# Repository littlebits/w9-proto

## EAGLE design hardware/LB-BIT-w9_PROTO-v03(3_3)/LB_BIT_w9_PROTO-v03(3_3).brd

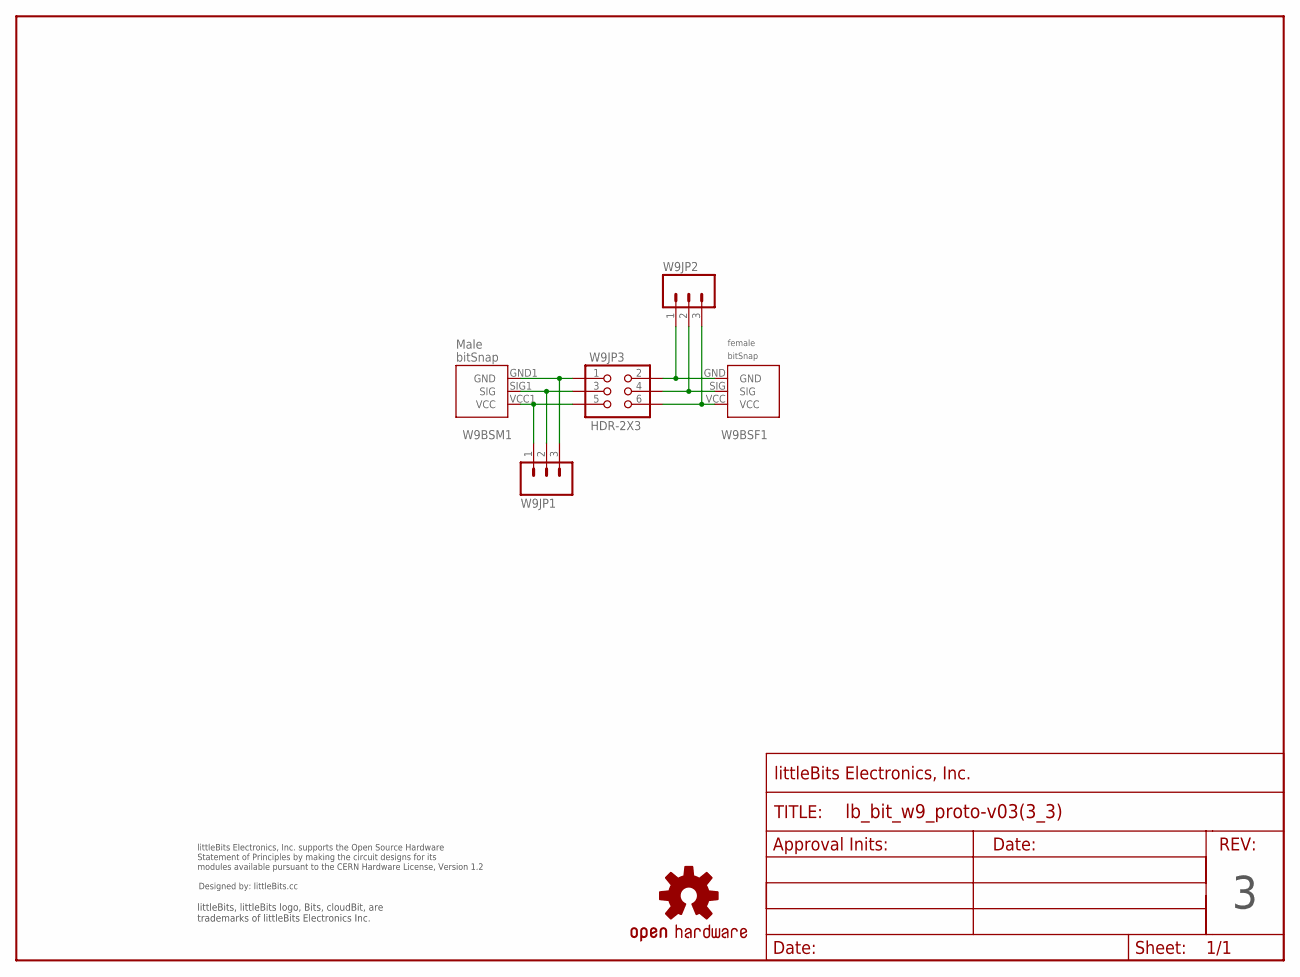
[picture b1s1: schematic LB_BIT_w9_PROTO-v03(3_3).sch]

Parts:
U$5: OSHWCREDIT
U$11: OSHW-LOGOL; OSHW-LOGO-L
U$13: FRAME-LETTER-OHWOHW; FABDWG01-OHW
W9BSF1: BITSNAP_V03_FEMALE"; BITSNAP_V03_FEMALE_NO_ARROW
W9BSM1: BITSNAP_V03_MALE
W9JP1, W9JP2: SCREW-TERMINAL-3PIN-2.54MM; 22-23-2031
W9JP3: HDR-2X3; 2X03

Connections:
GND1: W9BSM1.GND1 (GND), W9JP1.3, W9JP3.1
GND2: W9BSF1.GND, W9JP2.1, W9JP3.2
unnamed: W9BSM1.SIG1 (SIG), W9JP1.2, W9JP3.3
unnamed: W9BSM1.VCC1 (VCC), W9JP1.1, W9JP3.5
unnamed: W9BSF1.VCC, W9JP2.3, W9JP3.6
unnamed: W9BSF1.SIG, W9JP2.2, W9JP3.4

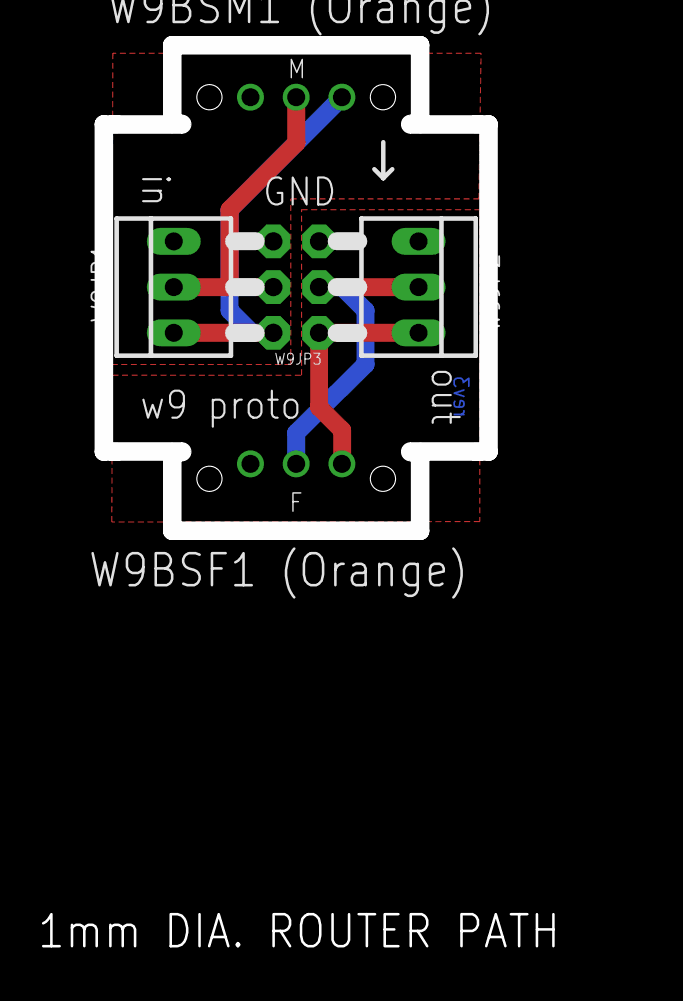
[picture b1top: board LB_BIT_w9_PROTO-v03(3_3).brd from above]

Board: 2 copper layers, 32.9 x 50.6 mm, 10 parts (0 on the bottom side), 6 nets.

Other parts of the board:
DRILEGEND: DRILEGEND
U$1: OSHW_FILLX150_NOTEXT

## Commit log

2014-11-12 First commit, added hardware files
2014-11-13 Added readme

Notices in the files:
parts and their libraries:
LITTLEBITS: modules available pursuant to the CERN Hardware License,
Version 1.2
LITTLEBITS: modules available pursuant to the CERN Hardware License, Version 1.2
